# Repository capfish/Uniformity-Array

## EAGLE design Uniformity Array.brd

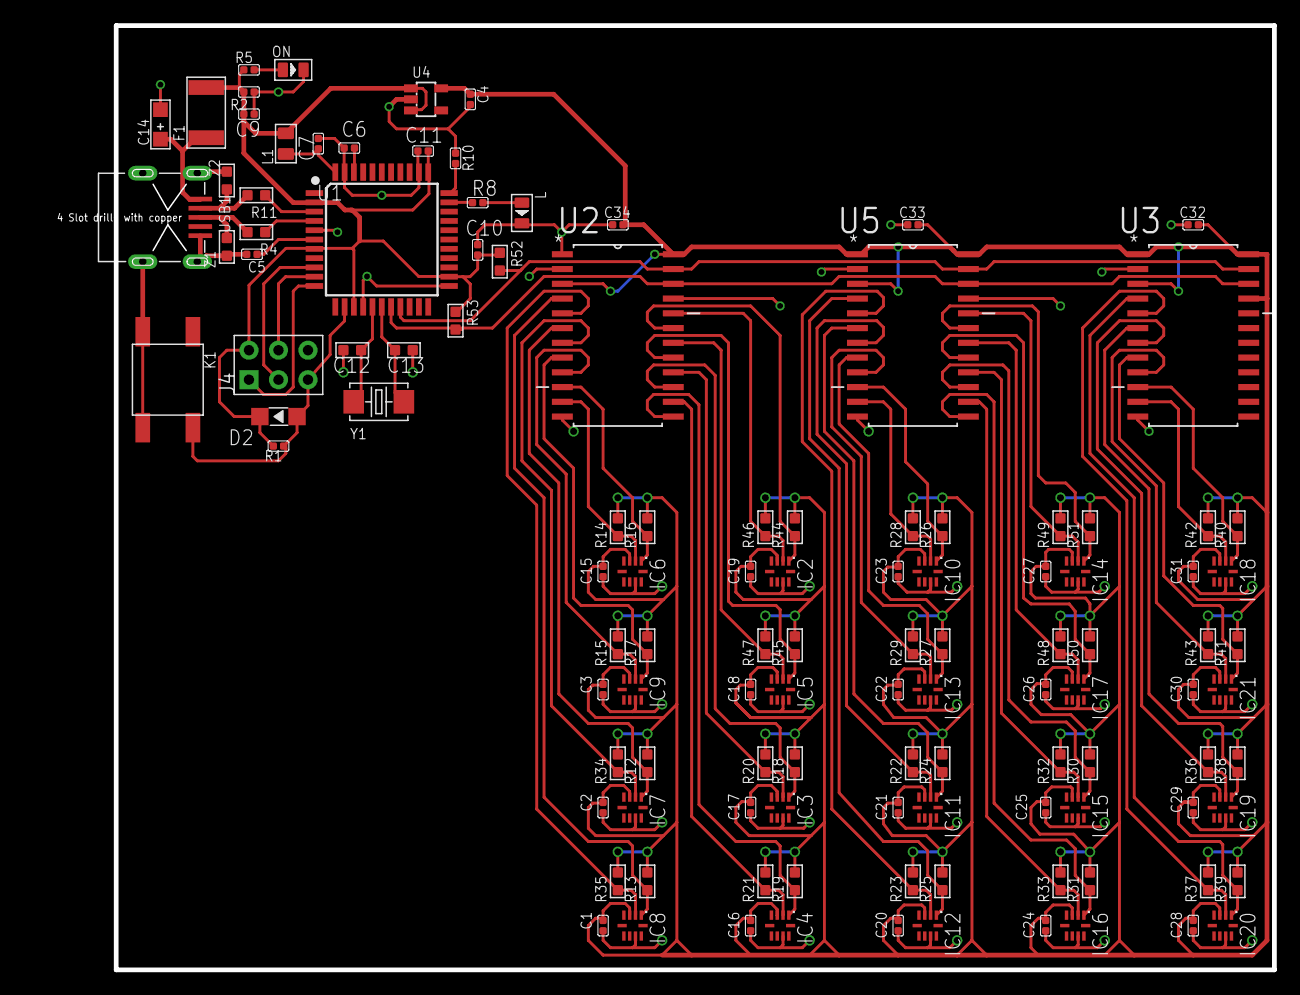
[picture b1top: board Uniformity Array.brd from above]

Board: 2 copper layers, 99.7 x 81.3 mm, 118 parts (0 on the bottom side), 63 nets.

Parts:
C1, C2, C3, C4, C5, C7, C15, C16, C17, C18, C19, C20, C21, C22, C23, C24, C25, C26, C27, C28, C29, C30, C31, C32, C33, C34: 1uf; C0402
C6, C9, C10, C11: 100nf; C0402
C12: 10pf; C0603
C13: 4.7PF; C0603
C14: 22uf; AVX-A
D2: 75V 150MA; LED-1206
F1: MF-MSMF050-2; F1812
IC2, IC3, IC4, IC5, IC6, IC7, IC8, IC9, IC10, IC11, IC12, IC13, IC14, IC15, IC16, IC17, IC18, IC19, IC20, IC21: SI1145; QFN-10
J4: 2x3p-2.54; H2X3-2.54
K1: DTSM-62K-S-V-T/R; SW4-SMD-6.0X6.0X5.0MM
L: GREEN-0805; LED-0805
L1: 330R-1500MA; L0805
ON: CLEAR-BLUE-0805; LED-0805
R1, R2, R10: 10K; R0402
R4, R11: 22R; R0603
R5, R8: 1K; R0402
R12, R13, R14, R15, R16, R17, R18, R19, R20, R21, R22, R23, R24, R25, R26, R27, R28, R29, R30, R31, R32, R33, R34, R35, R36, R37, R38, R39, R40, R41, R42, R43, R44, R45, R46, R47, R48, R49, R50, R51, R52, R53: 510R; R0603
U1: ATMEGA32U4-TQFP44; TQFP44-0.8-9.6X9.6MM
U2, U3, U5: PCA9547D,112; SOIC127P1032X265-24N
U4: LP2985-33DBVR; SOT-23-5
USB1: ST-USB-013A; MINIUSB5+4P-0.8-90D
Y1: 16MHZ; X2-SMD-5.0X3.2X1.3MM
Z1, Z2: 5V-28V; R0603

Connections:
3V3: C1.1, C2.1, C3.1, C4.1, C15.1, C16.1, C17.1, C18.1, C19.1, C20.1, C21.1, C22.1, C23.1, C24.1, C25.1, C26.1, C27.1, C28.1, C29.1, C30.1, C31.1, C32.2, C33.2, C34.2, IC2.3, IC3.3, IC4.3, IC5.3, IC6.3, IC7.3, IC8.3, IC9.3, IC10.3, IC11.3, IC12.3, IC13.3, IC14.3, IC15.3, IC16.3, IC17.3, IC18.3, IC19.3, IC20.3, IC21.3, R12.1, R13.1, R14.1, R15.1, R16.1, R17.1, R18.1, R19.1, R20.1, R21.1, R22.1, R23.1, R24.1, R25.1, R26.1, R27.1, R28.1, R29.1, R30.1, R31.1, R32.1, R33.1, R34.1, R35.1, R36.1, R37.1, R38.1, R39.1, R40.1, R41.1, R42.1, R43.1, R44.1, R45.1, R46.1, R47.1, R48.1, R49.1, R50.1, R51.1, U2.3, U2.24, U3.1, U3.3, U3.21, U3.24, U4.5, U5.1, U5.3, U5.24
AREF: C6.1, U1.42
AVCC: C7.1, L1.1, U1.44
D+: R4.1, USB1.3, Z1.1
D-: R11.1, USB1.2, Z2.1
GND: C1.2, C2.2, C3.2, C4.2, C5.2, C6.2, C7.2, C9.2, C10.2, C11.2, C12.1, C13.1, C14.-, C15.2, C16.2, C17.2, C18.2, C19.2, C20.2, C21.2, C22.2, C23.2, C24.2, C25.2, C26.2, C27.2, C28.2, C29.2, C30.2, C31.2, C32.1, C33.1, C34.1, IC2.8, IC3.8, IC4.8, IC5.8, IC6.8, IC7.8, IC8.8, IC9.8, IC10.8, IC11.8, IC12.8, IC13.8, IC14.8, IC15.8, IC16.8, IC17.8, IC18.8, IC19.8, IC20.8, IC21.8, J4.4, K1.2, K1.3, L.-, ON.-, R2.1, R10.1, U1.5, U1.15, U1.23, U1.35, U1.43, U2.1, U2.2, U2.12, U2.21, U3.2, U3.12, U4.2, U5.2, U5.12, U5.21, USB1.5, USB1.GND@1, USB1.GND@2, USB1.GND@3, USB1.GND@4, Z1.2, Z2.2
IO13*: R8.1, U1.32
MISO: J4.1, U1.11
MOSI: J4.5, U1.10
unnamed: IC5.2, R47.2, U2.18
unnamed: ON.+, R5.2
unnamed: IC5.1, R45.2, U2.17
unnamed: R10.2, U1.33
unnamed: L.+, R8.2
unnamed: IC7.1, R12.2, U2.6
unnamed: IC7.2, R34.2, U2.7
unnamed: IC8.1, R13.2, U2.4
unnamed: IC8.2, R35.2, U2.5
unnamed: IC3.1, R18.2, U2.15
unnamed: IC4.1, R19.2, U2.13
unnamed: IC4.2, R21.2, U2.14
unnamed: IC3.2, R20.2, U2.16
unnamed: IC9.1, R17.2, U2.8
unnamed: IC9.2, R15.2, U2.9
unnamed: IC6.1, R16.2, U2.10
unnamed: IC6.2, R14.2, U2.11
unnamed: IC2.1, R44.2, U2.19
unnamed: IC2.2, R46.2, U2.20
unnamed: IC11.1, R24.2, U5.6
unnamed: IC12.1, R25.2, U5.4
unnamed: IC12.2, R23.2, U5.5
unnamed: IC11.2, R22.2, U5.7
unnamed: IC13.1, R27.2, U5.8
unnamed: IC13.2, R29.2, U5.9
unnamed: IC10.1, R26.2, U5.10
unnamed: IC10.2, R28.2, U5.11
unnamed: IC15.1, R30.2, U5.15
unnamed: IC16.1, R31.2, U5.13
unnamed: IC16.2, R33.2, U5.14
unnamed: IC15.2, R32.2, U5.16
unnamed: IC17.1, R50.2, U5.17
unnamed: IC17.2, R48.2, U5.18
unnamed: IC14.1, R51.2, U5.19
unnamed: IC14.2, R49.2, U5.20
unnamed: IC19.1, R38.2, U3.6
unnamed: IC20.1, R39.2, U3.4
unnamed: IC20.2, R37.2, U3.5
unnamed: IC19.2, R36.2, U3.7
unnamed: IC21.1, R41.2, U3.8
unnamed: IC21.2, R43.2, U3.9
unnamed: IC18.1, R40.2, U3.10
unnamed: IC18.2, R42.2, U3.11
RD+: R4.2, U1.4
RD-: R11.2, U1.3
RESET: D2.+, J4.3, K1.4, R1.2, U1.13
SCK: J4.2, U1.9
SCL: R53.1, U1.18, U2.22, U3.22, U5.22
SDA: R52.1, U1.19, U2.23, U3.23, U5.23
UCAP: C5.1, U1.6
VUSB: C9.1, C10.1, C11.1, D2.-, F1.2, J4.6, L1.2, R1.1, R2.2, R5.1, R52.2, R53.2, U1.2, U1.7, U1.14, U1.24, U1.34, U4.1, U4.3
VUSBD: C14.+, F1.1, USB1.1
XTAL1: C13.2, U1.17, Y1.2
XTAL2: C12.2, U1.16, Y1.1

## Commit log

2016-03-21 schematiced
2016-03-22 sensors placed
2016-03-24 routed the sensors
2016-03-28 routed! (also pulled ~RESET hight)
2016-03-28 replaced USB, gerbered, BOM
